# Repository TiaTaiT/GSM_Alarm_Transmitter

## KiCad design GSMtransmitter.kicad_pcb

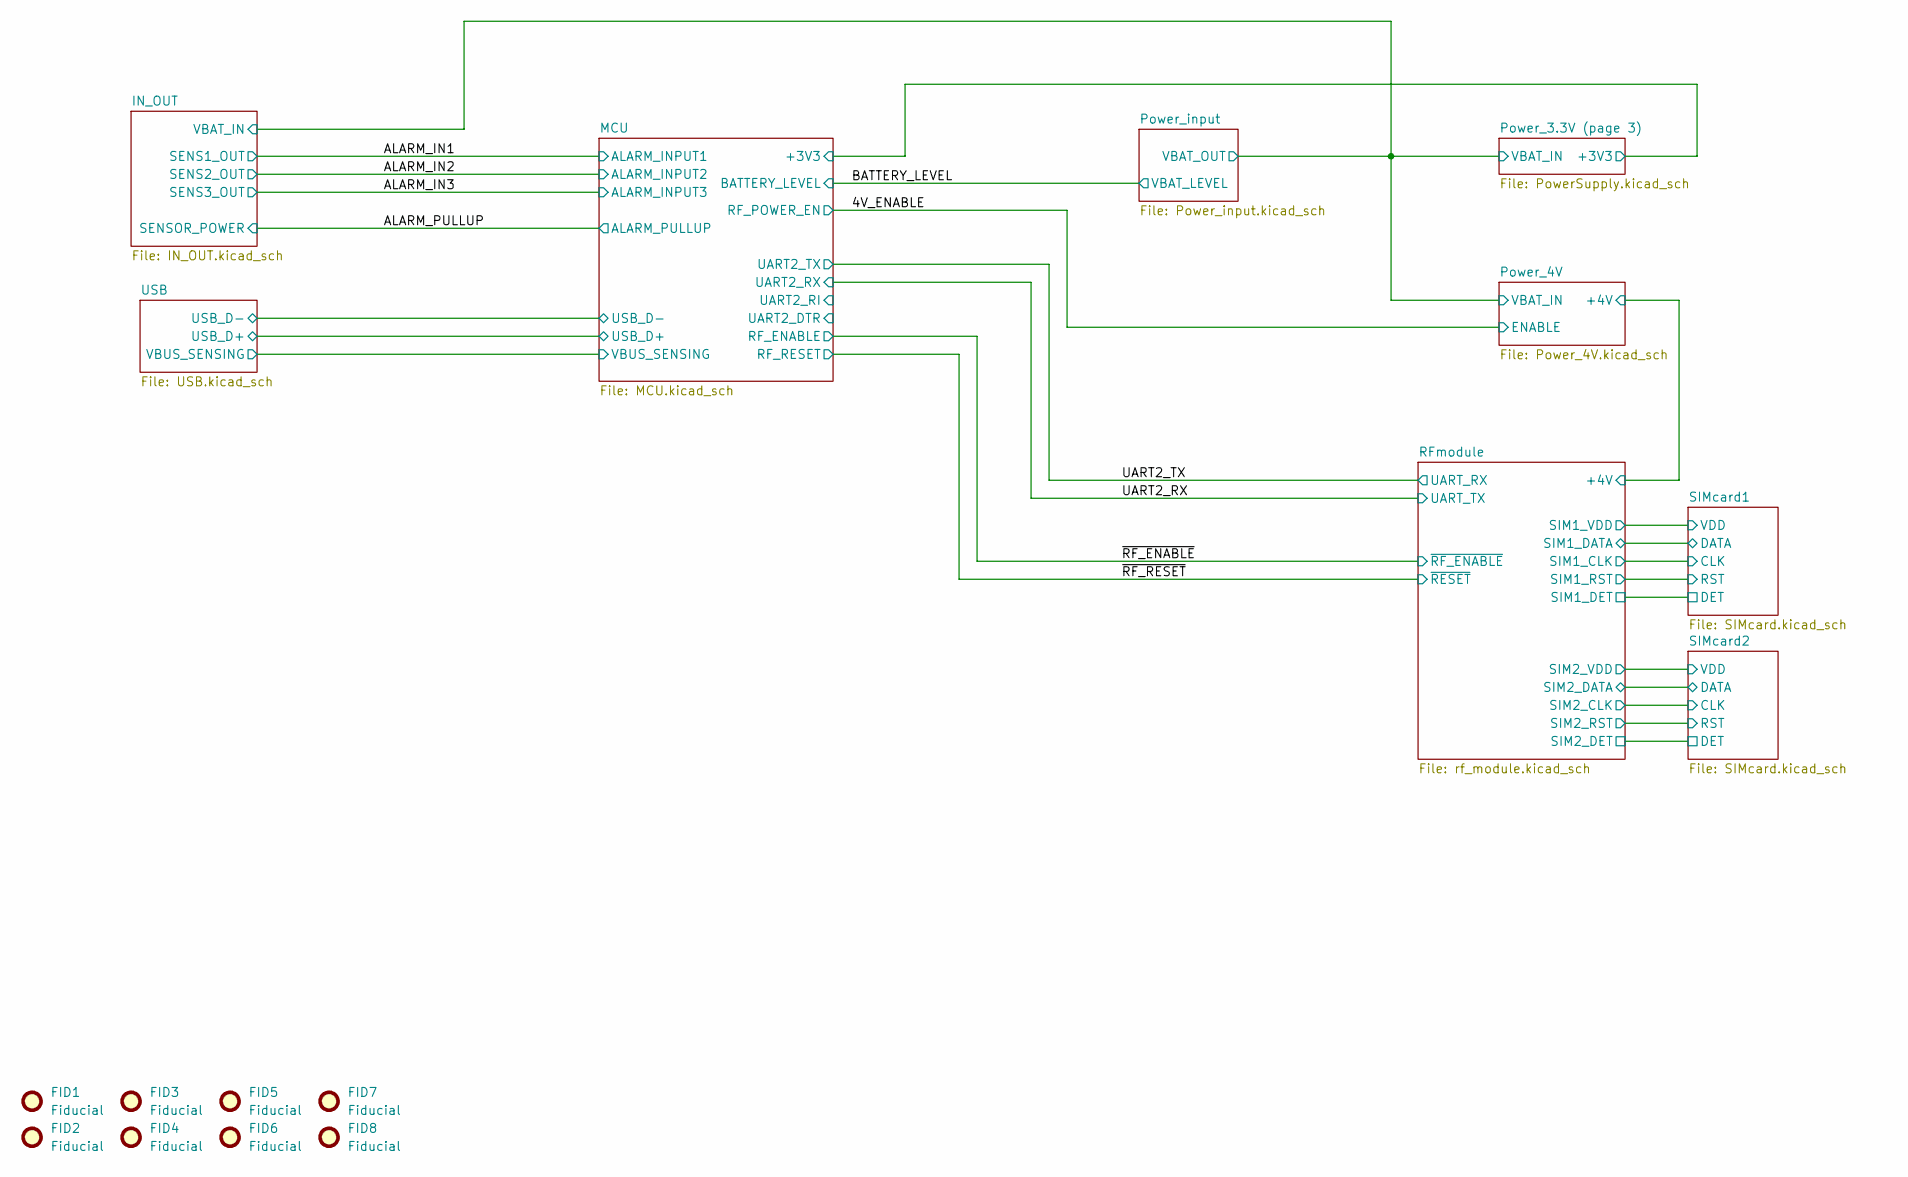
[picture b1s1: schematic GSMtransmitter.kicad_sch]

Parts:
FID1, FID2, FID3, FID4, FID5, FID6, FID7, FID8: Fiducial; Fiducial_1mm_Mask2mm

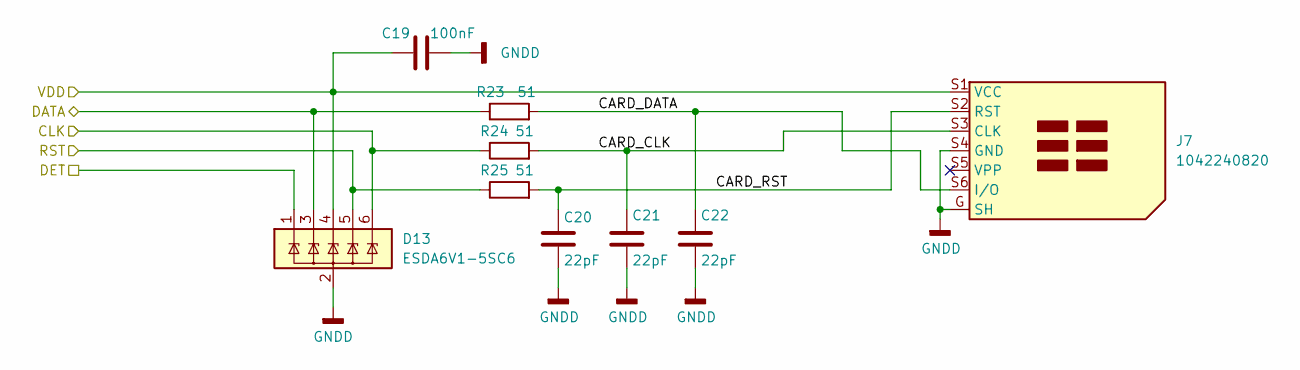
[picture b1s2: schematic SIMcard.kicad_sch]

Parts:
C19: 100nF; C_0805_2012Metric_Pad1.18x1.45mm_HandSolder; MPN CC0805KRX7R8BB104
C20, C21, C22: 22pF; C_0805_2012Metric_Pad1.18x1.45mm_HandSolder; MPN CC0805KRNPO9BN220
D13: ESDA6V1-5SC6; SOT-23-6; MPN ESDA6V1-5SC6
J7: 1042240820; 1042240820_MOLEX; MPN 1042240820
R23, R24, R25: 51; R_0805_2012Metric_Pad1.20x1.40mm_HandSolder; MPN RC0805JR-0751RL

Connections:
/RFmodule/SIM1_CLK: D13.6 (IO5), R24.1; also elsewhere on the board
/RFmodule/SIM1_DATA: D13.3 (IO2), R23.1; also elsewhere on the board
/RFmodule/SIM1_DET: D13.1 (IO1); also elsewhere on the board
/RFmodule/SIM1_RST: D13.5 (IO4), R25.1; also elsewhere on the board
/RFmodule/SIM1_VDD: C19.2, D13.4 (IO3), J7.S1 (VCC); also elsewhere on the board
/SIMcard1/CARD_CLK: C21.2, J7.S3 (CLK), R24.2
/SIMcard1/CARD_DATA: C22.2, J7.S6 (I/O), R23.2
/SIMcard1/CARD_RST: C20.2, J7.S2 (RST), R25.2
GNDD: C19.1, C20.1, C21.1, C22.1, D13.2 (GND), J7.G (SH), J7.S4 (GND); also elsewhere on the board

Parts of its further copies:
C23: 100nF; C_0805_2012Metric_Pad1.18x1.45mm_HandSolder; MPN CC0805KRX7R8BB104
C24, C25, C26: 22pF; C_0805_2012Metric_Pad1.18x1.45mm_HandSolder; MPN CC0805KRNPO9BN220
D14: ESDA6V1-5SC6; SOT-23-6; MPN ESDA6V1-5SC6
J8: 1042240820; 1042240820_MOLEX; MPN 1042240820
R26, R27, R28: 51; R_0805_2012Metric_Pad1.20x1.40mm_HandSolder; MPN RC0805JR-0751RL

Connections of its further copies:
/RFmodule/SIM2_CLK: D14.6 (IO5), R27.1; also elsewhere on the board
/RFmodule/SIM2_DATA: D14.3 (IO2), R26.1; also elsewhere on the board
/RFmodule/SIM2_DET: D14.1 (IO1); also elsewhere on the board
/RFmodule/SIM2_RST: D14.5 (IO4), R28.1; also elsewhere on the board
/RFmodule/SIM2_VDD: C23.2, D14.4 (IO3), J8.S1 (VCC); also elsewhere on the board
/SIMcard2/CARD_CLK: C25.2, J8.S3 (CLK), R27.2
/SIMcard2/CARD_DATA: C26.2, J8.S6 (I/O), R26.2
/SIMcard2/CARD_RST: C24.2, J8.S2 (RST), R28.2
GNDD: C23.1, C24.1, C25.1, C26.1, D14.2 (GND), J8.G (SH), J8.S4 (GND); also elsewhere on the board

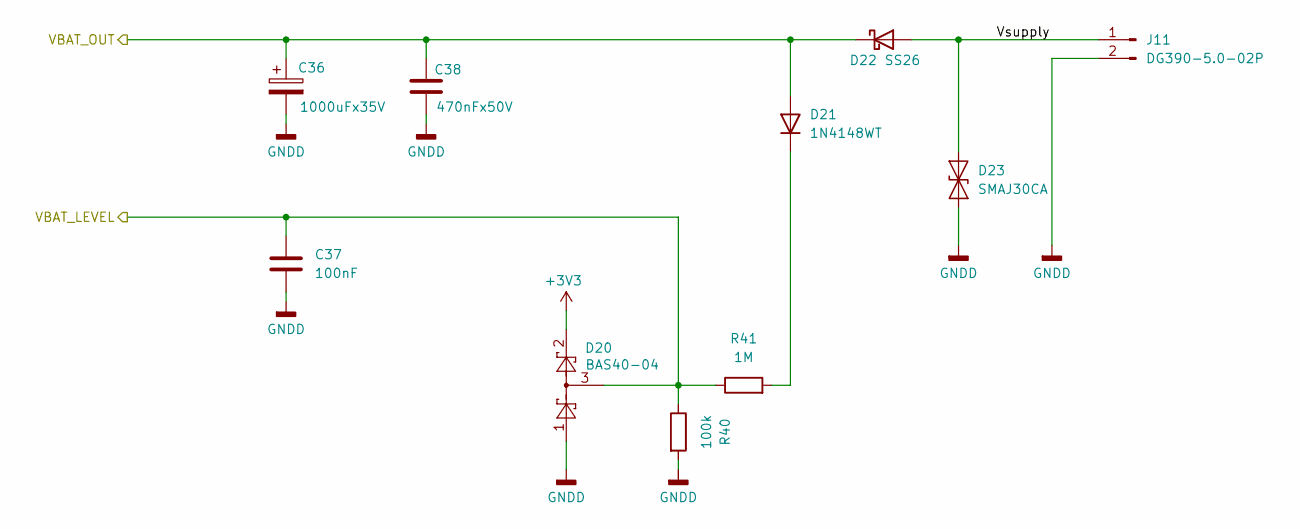
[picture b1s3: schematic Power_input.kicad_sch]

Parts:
C36: 1000uFx35V; CP_Radial_D12.5mm_P5.00mm; MPN B41851F7108M000
C37: 100nF; C_0805_2012Metric_Pad1.18x1.45mm_HandSolder; MPN CC0805KRX7R8BB104
C38: 470nFx50V; C_0805_2012Metric_Pad1.18x1.45mm_HandSolder; MPN CC0805ZRY5V9BB474
D20: BAS40-04; SOT-23; MPN BAS40-04-7-F
D21: 1N4148WT; D_SOD-523; MPN 1N4148WT-7
D22: SS26; D_SMA; MPN SS26
D23: SMAJ30CA; D_SMA; MPN SMAJ30CA
J11: DG390-5.0-02P; DEGSON_DG390-5.0-02P_1x02_P5.0mm_Vertical; MPN DG390-5.0-02P
R40: 100k; R_0805_2012Metric_Pad1.20x1.40mm_HandSolder; MPN RC0805JR-07100KL
R41: 1M; R_0805_2012Metric_Pad1.20x1.40mm_HandSolder; MPN RC0805JR-071ML

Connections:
+3V3: D20.2; also elsewhere on the board
/BATTERY_LEVEL: C37.2, D20.3, R40.1, R41.1; also elsewhere on the board
/IN_OUT/VBAT_IN: C36.1, C38.1, D21.2 (A), D22.1 (K); also elsewhere on the board
/Power_input/Vsupply: D22.2 (A), D23.2 (A2), J11.1
GNDD: C36.2, C37.1, C38.2, D20.1, D23.1 (A1), J11.2, R40.2; also elsewhere on the board
unnamed: D21.1 (K), R41.2

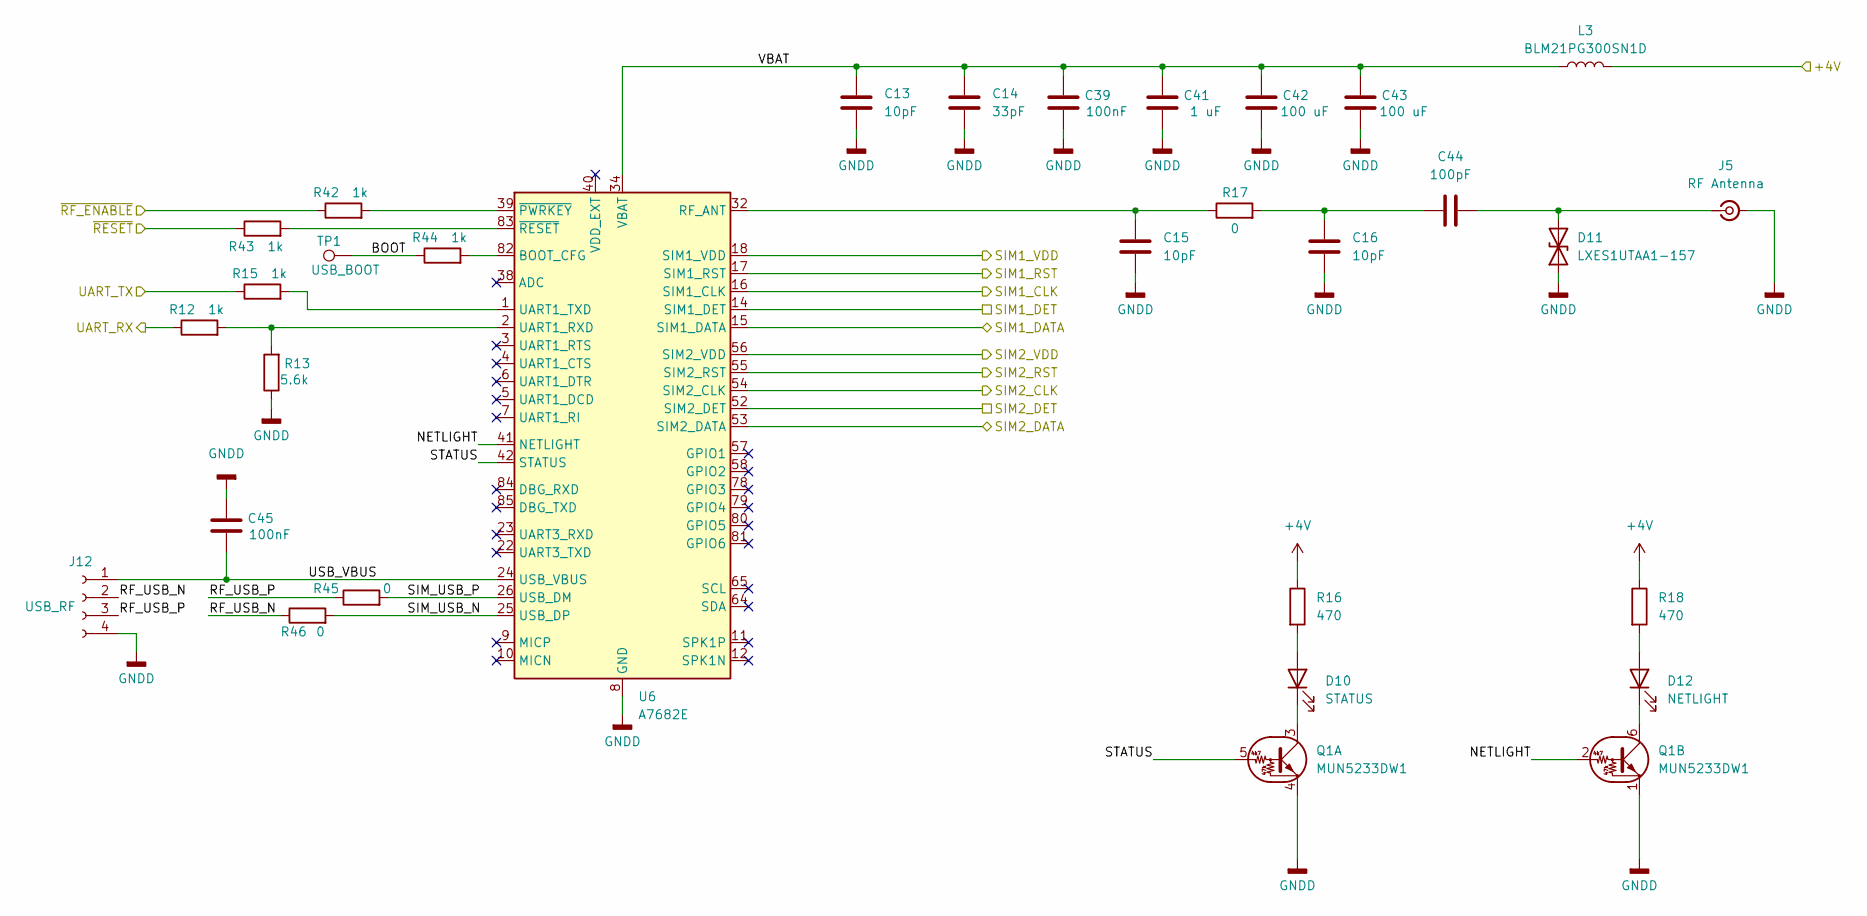
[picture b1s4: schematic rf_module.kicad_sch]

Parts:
C13: 10pF; C_0805_2012Metric_Pad1.18x1.45mm_HandSolder; MPN CC0805JRNPO9BN100
C14: 33pF; C_0805_2012Metric_Pad1.18x1.45mm_HandSolder; MPN CC0805JRNPO9BN330
C15, C16: 10pF; C_0402_1005Metric; MPN CC0402JRNPO9BN100
C39, C45: 100nF; C_0805_2012Metric_Pad1.18x1.45mm_HandSolder; MPN CC0805KRX7R8BB104
C41: 1 uF; C_0805_2012Metric_Pad1.18x1.45mm_HandSolder; MPN CC0805KFX7R9BB105
C42, C43: 100 uF; C_1206_3216Metric_Pad1.33x1.80mm_HandSolder; MPN CC1206MKX5R5BB107
C44: 100pF; C_0402_1005Metric; MPN CC0402JRNPO9BN101
D10: STATUS; LED_0805_2012Metric_Pad1.15x1.40mm_HandSolder; MPN FYLS-0805URC
D11: LXES1UTAA1-157; D_01005_0402Metric; MPN LXES1UTAA1-157
D12: NETLIGHT; LED_0805_2012Metric_Pad1.15x1.40mm_HandSolder; MPN FYLS-0805URC
J5: RF Antenna; SMA_HJ-SMA405; MPN HJ-SMA405
J12: USB_RF; PinHeader_1x04_P1.27mm_Vertical
L3: BLM21PG300SN1D; L_0805_2012Metric; MPN BLM21PG300SN1D
Q1: MUN5233DW1; SOT-363_SC-70-6; MPN MMUN2133LT1G
R12, R15, R42, R43, R44: 1k; R_0805_2012Metric_Pad1.20x1.40mm_HandSolder; MPN RC0805JR-071KL
R13: 5.6k; R_0805_2012Metric_Pad1.20x1.40mm_HandSolder; MPN RC0805JR-075K6L
R16, R18: 470; R_0805_2012Metric_Pad1.20x1.40mm_HandSolder; MPN RC0805JR-07470RL
R17, R45, R46: 0; R_0402_1005Metric; MPN RC0402JR-070RL
TP1: USB_BOOT; TestPoint_Pad_D2.0mm
U6: A7682E; SIMCom_A7682E_LGA-85; MPN A7682E

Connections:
+4V: L3.2, R16.1, R18.1; also elsewhere on the board
/RFmodule/BOOT: R44.1, TP1.1 (1_1)
/RFmodule/NETLIGHT: Q1.2 (B), U6.41 (NETLIGHT)
/RFmodule/RF_USB_N: J12.2, R46.1
/RFmodule/RF_USB_P: J12.3, R45.1
/RFmodule/SIM1_CLK: U6.16 (SIM1_CLK); also elsewhere on the board
/RFmodule/SIM1_DATA: U6.15 (SIM1_DATA); also elsewhere on the board
/RFmodule/SIM1_DET: U6.14 (SIM1_DET); also elsewhere on the board
/RFmodule/SIM1_RST: U6.17 (SIM1_RST); also elsewhere on the board
/RFmodule/SIM1_VDD: U6.18 (SIM1_VDD); also elsewhere on the board
/RFmodule/SIM2_CLK: U6.54 (SIM2_CLK); also elsewhere on the board
/RFmodule/SIM2_DATA: U6.53 (SIM2_DATA); also elsewhere on the board
/RFmodule/SIM2_DET: U6.52 (SIM2_DET); also elsewhere on the board
/RFmodule/SIM2_RST: U6.55 (SIM2_RST); also elsewhere on the board
/RFmodule/SIM2_VDD: U6.56 (SIM2_VDD); also elsewhere on the board
/RFmodule/SIM_USB_N: R46.2, U6.25 (USB_DP)
/RFmodule/SIM_USB_P: R45.2, U6.26 (USB_DM)
/RFmodule/STATUS: Q1.5 (B), U6.42 (STATUS)
/RFmodule/USB_VBUS: C45.1, J12.1, U6.24 (USB_VBUS)
/RFmodule/VBAT: C13.2, C14.2, C39.2, C41.2, C42.2, C43.2, L3.1, U6.34 (VBAT), U6.35 (VBAT)
/UART2_RX: R15.1; also elsewhere on the board
/UART2_TX: R12.1; also elsewhere on the board
/~RF_ENABLE: R42.1; also elsewhere on the board
/~RF_RESET: R43.1; also elsewhere on the board
GNDD: C13.1, C14.1, C15.1, C16.1, C39.1, C41.1, C42.1, C43.1, C45.2, D11.1 (A1), J5.2 (Ext), J12.4, Q1.1 (E), Q1.4 (E), R13.1, U6.8 (GND), U6.13 (GND), U6.19 (GND), U6.21 (GND), U6.27 (GND), U6.30 (GND), U6.31 (GND), U6.33 (GND), U6.36 (GND), U6.37 (GND), U6.45 (GND), U6.63 (GND), U6.66 (GND), U6.67 (GND), U6.69 (GND), U6.70 (GND), U6.71 (GND), U6.72 (GND), U6.73 (GND), U6.74 (GND), U6.75 (GND), U6.76 (GND), U6.77 (GND); also elsewhere on the board
unnamed: C16.2, C44.2, R17.2
unnamed: D10.2 (A), R16.2
unnamed: D10.1 (K), Q1.3 (C)
unnamed: C44.1, D11.2 (A2), J5.1 (In)
unnamed: D12.2 (A), R18.2
unnamed: D12.1 (K), Q1.6 (C)
unnamed: R44.2, U6.82 (BOOT_CFG)
unnamed: C15.2, R17.1, U6.32 (RF_ANT)
unnamed: R12.2, R13.2, U6.2 (UART1_RXD)
unnamed: R15.2, U6.1 (UART1_TXD)
unnamed: R42.2, U6.39 (~PWRKEY)
unnamed: R43.2, U6.83 (~RESET)

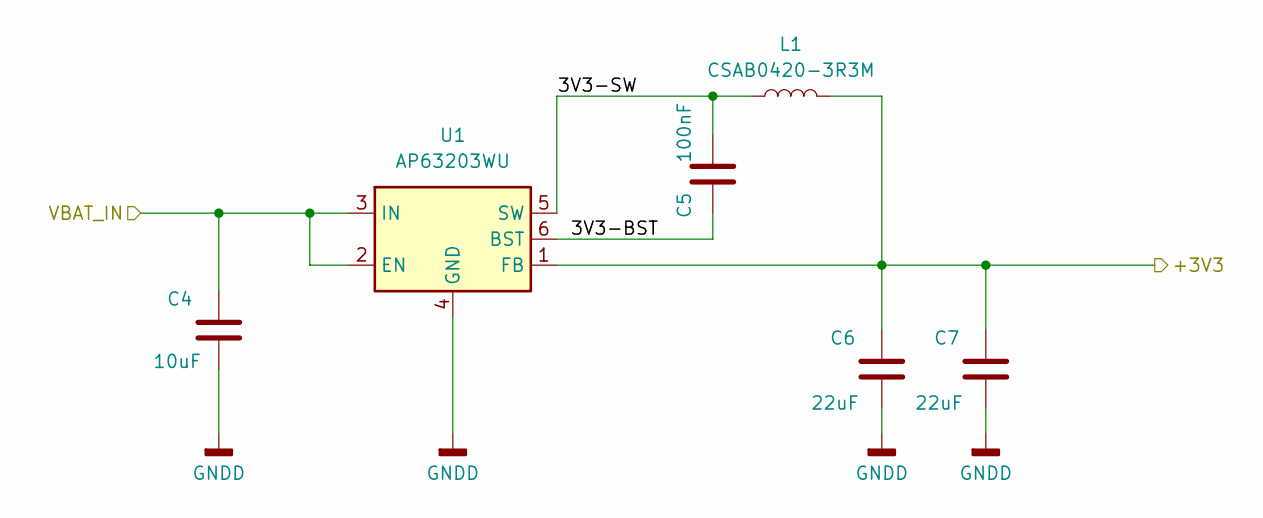
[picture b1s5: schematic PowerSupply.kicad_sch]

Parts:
C4: 10uF; C_0805_2012Metric_Pad1.18x1.45mm_HandSolder; MPN CC0805KKX5R9BB106
C5: 100nF; C_0805_2012Metric_Pad1.18x1.45mm_HandSolder; MPN CC0805KRX7R8BB104
C6, C7: 22uF; C_0805_2012Metric_Pad1.18x1.45mm_HandSolder; MPN CC0805MKX5R8BB226
L1: CSAB0420-3R3M; CSAB0420-4.4x4.4mm; MPN CSAB0420-3R3M
U1: AP63203WU; TSOT-23-6; MPN AP63203WU

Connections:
+3V3: C6.2, C7.2, L1.2, U1.1 (FB); also elsewhere on the board
/IN_OUT/VBAT_IN: C4.2, U1.2 (EN), U1.3 (IN); also elsewhere on the board
/Power_3.3V (page 3)/3V3-BST: C5.1, U1.6 (BST)
/Power_3.3V (page 3)/3V3-SW: C5.2, L1.1, U1.5 (SW)
GNDD: C4.1, C6.1, C7.1, U1.4 (GND); also elsewhere on the board

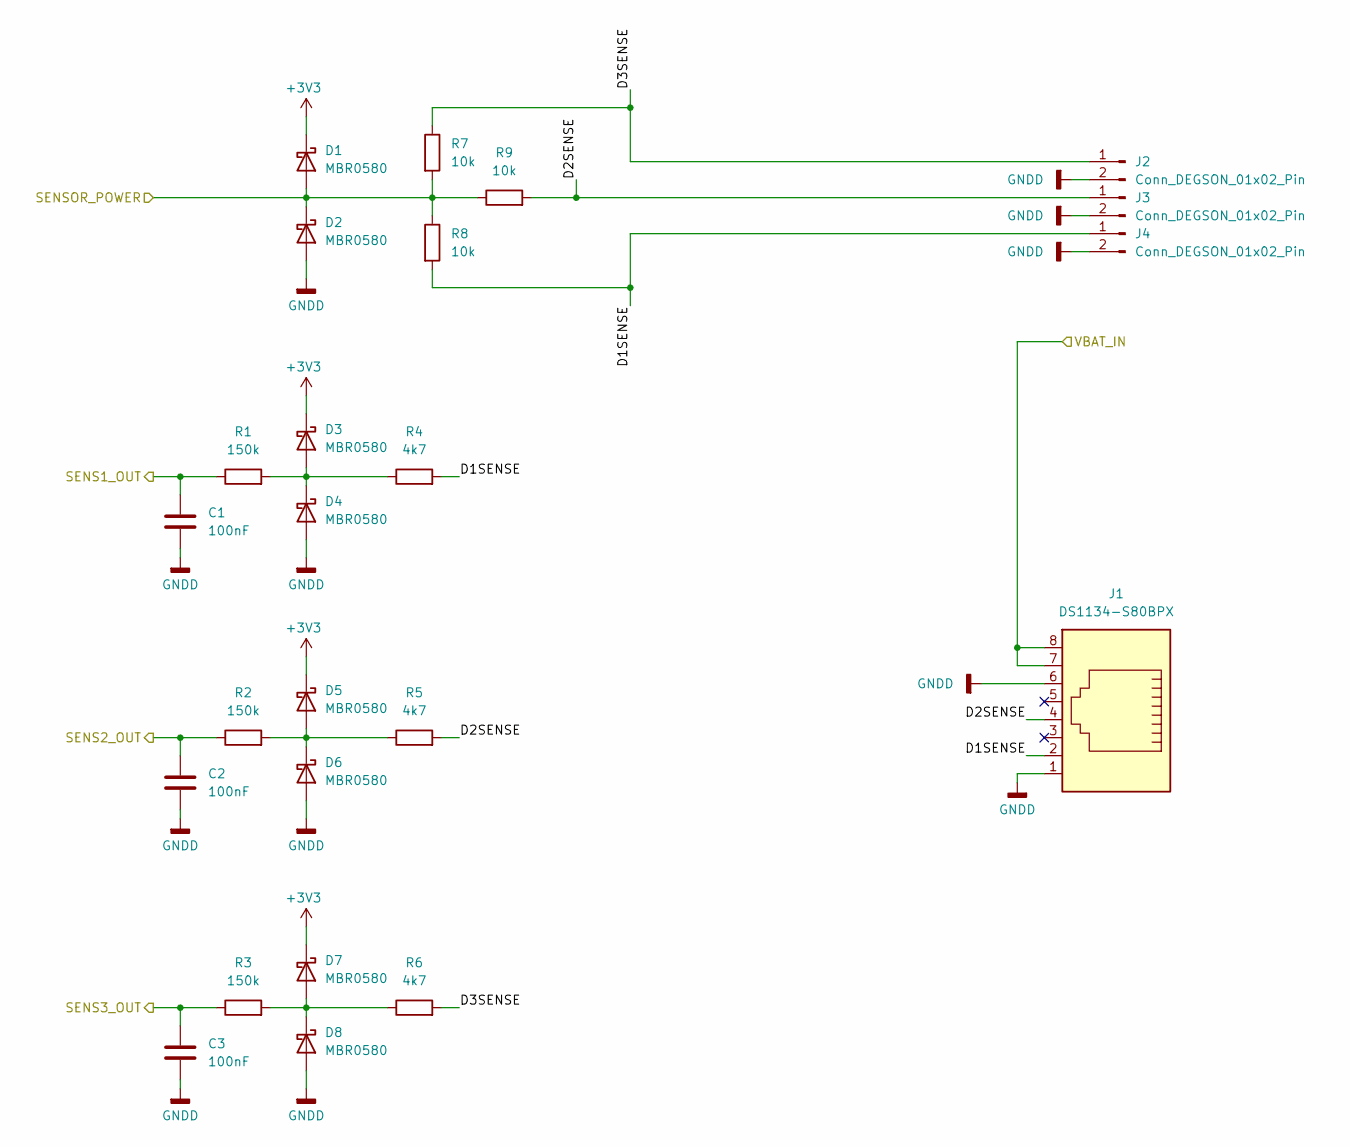
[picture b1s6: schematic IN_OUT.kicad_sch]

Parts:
C1, C2, C3: 100nF; C_0805_2012Metric_Pad1.18x1.45mm_HandSolder; MPN CC0805KRX7R8BB104
D1, D2, D3, D4, D5, D6, D7, D8: MBR0580; D_SOD-123; MPN MBR0580
J1: DS1134-S80BPX; RJ45_DS1134-8P8CX_Horizontal; MPN DS1134-S80BPX
J2, J3, J4: Conn_DEGSON_01x02_Pin; DEGSON_DG390-5.0-02P_1x02_P5.0mm_Vertical; MPN DG390-5.0-02P
R1, R2, R3: 150k; R_0805_2012Metric_Pad1.20x1.40mm_HandSolder; MPN RC0805JR-07150KL
R4, R5, R6: 4k7; R_0805_2012Metric_Pad1.20x1.40mm_HandSolder; MPN RC0805JR-074K7L
R7, R8, R9: 10k; R_0805_2012Metric_Pad1.20x1.40mm_HandSolder; MPN RC0805FR-0710KL

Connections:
+3V3: D1.1 (K), D3.1 (K), D5.1 (K), D7.1 (K); also elsewhere on the board
/ALARM_IN1: C1.2, R1.1; also elsewhere on the board
/ALARM_IN2: C2.2, R2.1; also elsewhere on the board
/ALARM_IN3: C3.2, R3.1; also elsewhere on the board
/ALARM_PULLUP: D1.2 (A), D2.1 (K), R7.2, R8.1, R9.1; also elsewhere on the board
/IN_OUT/D1SENSE: J1.2, J4.1, R4.2, R8.2
/IN_OUT/D2SENSE: J1.4, J3.1, R5.2, R9.2
/IN_OUT/D3SENSE: J2.1, R6.2, R7.1
/IN_OUT/VBAT_IN: J1.7, J1.8; also elsewhere on the board
GNDD: C1.1, C2.1, C3.1, D2.2 (A), D4.2 (A), D6.2 (A), D8.2 (A), J1.1, J1.6, J2.2, J3.2, J4.2; also elsewhere on the board
unnamed: D3.2 (A), D4.1 (K), R1.2, R4.1
unnamed: D5.2 (A), D6.1 (K), R2.2, R5.1
unnamed: D7.2 (A), D8.1 (K), R3.2, R6.1

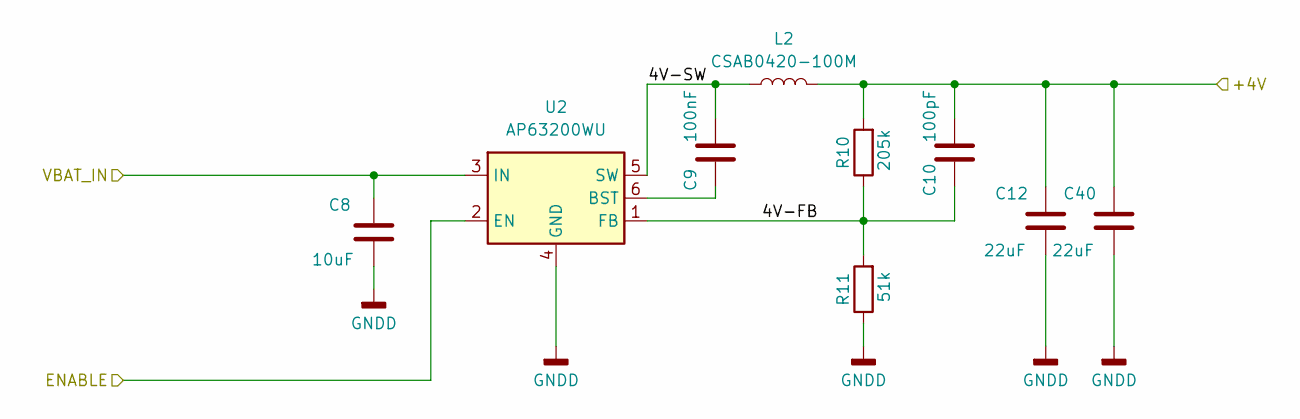
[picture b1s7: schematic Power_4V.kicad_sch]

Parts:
C8: 10uF; C_0805_2012Metric_Pad1.18x1.45mm_HandSolder; MPN CC0805KKX5R9BB106
C9: 100nF; C_0805_2012Metric_Pad1.18x1.45mm_HandSolder; MPN CC0805KRX7R8BB104
C10: 100pF; C_0805_2012Metric_Pad1.18x1.45mm_HandSolder; MPN CC0805JRNPO9BN101
C12, C40: 22uF; C_0805_2012Metric_Pad1.18x1.45mm_HandSolder; MPN CC0805MKX5R8BB226
L2: CSAB0420-100M; CSAB0420-4.4x4.4mm; MPN CSAB0420-100M
R10: 205k; R_0805_2012Metric_Pad1.20x1.40mm_HandSolder; MPN RC0805FR-07205KL
R11: 51k; R_0805_2012Metric_Pad1.20x1.40mm_HandSolder; MPN RC0805FR-0751KL
U2: AP63200WU; TSOT-23-6; MPN AP63200WU

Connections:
+4V: C10.2, C12.2, C40.2, L2.2, R10.2; also elsewhere on the board
/4V_ENABLE: U2.2 (EN); also elsewhere on the board
/IN_OUT/VBAT_IN: C8.2, U2.3 (IN); also elsewhere on the board
/Power_4V/4V-FB: C10.1, R10.1, R11.2, U2.1 (FB)
/Power_4V/4V-SW: C9.2, L2.1, U2.5 (SW)
GNDD: C8.1, C12.1, C40.1, R11.1, U2.4 (GND); also elsewhere on the board
unnamed: C9.1, U2.6 (BST)

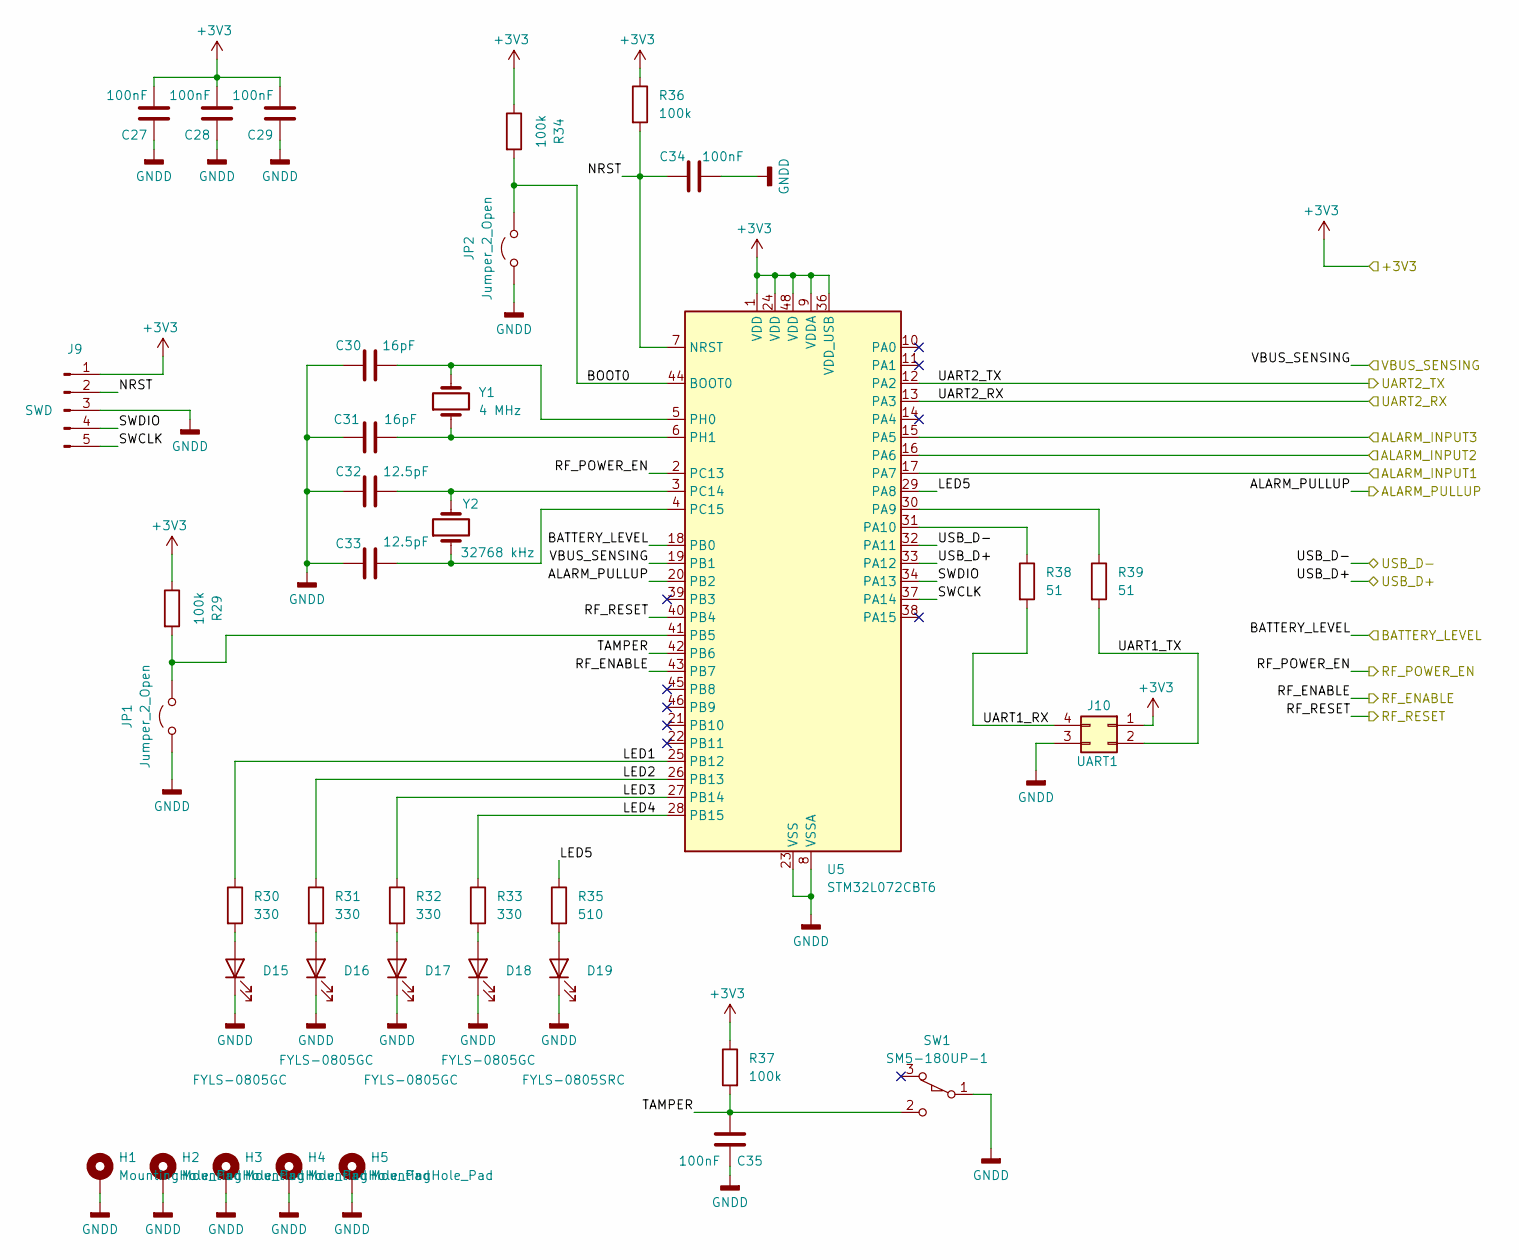
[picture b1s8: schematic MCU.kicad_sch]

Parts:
C27, C28, C29, C34, C35: 100nF; C_0805_2012Metric_Pad1.18x1.45mm_HandSolder; MPN CC0805KRX7R8BB104
C30, C31: 16pF; C_0805_2012Metric_Pad1.18x1.45mm_HandSolder; MPN CC0805JRNPO0BN160
C32, C33: 12.5pF; C_0805_2012Metric_Pad1.18x1.45mm_HandSolder; MPN CC0805JRNPO9BN120
D15, D16, D17, D18: FYLS-0805GC; LED_0805_2012Metric_Pad1.15x1.40mm_HandSolder; MPN FYLS-0805GC
D19: FYLS-0805SRC; LED_0805_2012Metric_Pad1.15x1.40mm_HandSolder; MPN FYLS-0805SRC
H1, H2, H3, H4, H5: MountingHole_Pad; MountingHole_3.2mm_M3_Pad_Via
J9: SWD; PinHeader_1x05_P2.54mm_Vertical; MPN DS1021-1x5SF11-B
J10: UART1; PinSocket_2x02_P2.54mm_Vertical; MPN DS1023-2*2SF11
JP1, JP2: Jumper_2_Open; PinHeader_1x02_P2.54mm_Vertical; MPN DS1021-1x2SF11-B
R29, R34, R36, R37: 100k; R_0805_2012Metric_Pad1.20x1.40mm_HandSolder; MPN RC0805JR-07100KL
R30, R31, R32, R33: 330; R_0805_2012Metric_Pad1.20x1.40mm_HandSolder; MPN RC0805JR-07330RL
R35: 510; R_0805_2012Metric_Pad1.20x1.40mm_HandSolder; MPN RC0805JR-07510RL
R38, R39: 51; R_0805_2012Metric_Pad1.20x1.40mm_HandSolder; MPN RC0805JR-0751RL
SW1: SM5-180UP-1; SW_XKB_SM5-180UP-1; MPN SM5-470UP-1
U5: STM32L072CBT6; LQFP-48_7x7mm_P0.5mm; MPN STM32L072CBT6
Y1: 4 MHz; Crystal_SMD_HC49-SD; MPN SJK-6C-4.000-16-30-100-C-50-H
Y2: 32768 kHz; Crystal_SMD_EuroQuartz_EQ161-2Pin_3.2x1.5mm_HandSoldering; MPN ABS07-32.768KHZ-T

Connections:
+3V3: C27.2, C28.2, C29.2, J9.1, J10.1, R29.1, R34.1, R36.1, R37.1, U5.1 (VDD), U5.9 (VDDA), U5.24 (VDD), U5.36 (VDD_USB), U5.48 (VDD); also elsewhere on the board
/4V_ENABLE: U5.2 (PC13); also elsewhere on the board
/ALARM_IN1: U5.17 (PA7); also elsewhere on the board
/ALARM_IN2: U5.16 (PA6); also elsewhere on the board
/ALARM_IN3: U5.15 (PA5); also elsewhere on the board
/ALARM_PULLUP: U5.20 (PB2); also elsewhere on the board
/BATTERY_LEVEL: U5.18 (PB0); also elsewhere on the board
/MCU/BOOT0: JP2.2 (B), R34.2, U5.44 (BOOT0)
/MCU/LED1: R30.1, U5.25 (PB12)
/MCU/LED2: R31.1, U5.26 (PB13)
/MCU/LED3: R32.1, U5.27 (PB14)
/MCU/LED4: R33.1, U5.28 (PB15)
/MCU/LED5: R35.1, U5.29 (PA8)
/MCU/NRST: C34.1, J9.2, R36.2, U5.7 (NRST)
/MCU/SWCLK: J9.5, U5.37 (PA14)
/MCU/SWDIO: J9.4, U5.34 (PA13)
/MCU/TAMPER: C35.2, R37.2, SW1.2 (B), U5.42 (PB6)
/MCU/UART1_RX: J10.4, R38.2
/MCU/UART1_TX: J10.2, R39.2
/MCU/USB_D+: U5.33 (PA12); also elsewhere on the board
/MCU/USB_D-: U5.32 (PA11); also elsewhere on the board
/MCU/VBUS_SENSING: U5.19 (PB1); also elsewhere on the board
/UART2_RX: U5.13 (PA3); also elsewhere on the board
/UART2_TX: U5.12 (PA2); also elsewhere on the board
/~RF_ENABLE: U5.43 (PB7); also elsewhere on the board
/~RF_RESET: U5.40 (PB4); also elsewhere on the board
GNDD: C27.1, C28.1, C29.1, C30.1, C31.1, C32.1, C33.1, C34.2, C35.1, D15.1 (K), D16.1 (K), D17.1 (K), D18.1 (K), D19.1 (K), H1.1 (1_1), H2.1 (1_1), H3.1 (1_1), H4.1 (1_1), H5.1 (1_1), J9.3, J10.3, JP1.1 (A), JP2.1 (A), SW1.1 (A), U5.8 (VSSA), U5.23 (VSS), U5.35 (VSS), U5.47 (VSS); also elsewhere on the board
unnamed: D15.2 (A), R30.2
unnamed: D16.2 (A), R31.2
unnamed: D17.2 (A), R32.2
unnamed: D18.2 (A), R33.2
unnamed: D19.2 (A), R35.2
unnamed: JP1.2 (B), R29.2, U5.41 (PB5)
unnamed: R39.1, U5.30 (PA9)
unnamed: R38.1, U5.31 (PA10)
unnamed: C32.2, U5.3 (PC14), Y2.2
unnamed: C33.2, U5.4 (PC15), Y2.1
unnamed: C30.2, U5.5 (PH0), Y1.2
unnamed: C31.2, U5.6 (PH1), Y1.1

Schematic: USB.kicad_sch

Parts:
C17, C18: 100nF; C_0805_2012Metric_Pad1.18x1.45mm_HandSolder; MPN CC0805KRX7R8BB104
J6: USB-C; JST_PH_B6B-PH-K_1x06_P2.00mm_Vertical; MPN B6B-PH-K
R19: 47k; R_0805_2012Metric_Pad1.20x1.40mm_HandSolder; MPN RC0805JR-0747KL
R20: 100k; R_0805_2012Metric_Pad1.20x1.40mm_HandSolder; MPN RC0805JR-07100KL
R21, R22: 5.1k; R_0805_2012Metric_Pad1.20x1.40mm_HandSolder; MPN RC0805JR-075K1L
U4: USBLC6-2SC6; SOT-23-6; MPN USBLC6-2SC6

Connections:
/MCU/USB_D+: U4.4 (I/O2); also elsewhere on the board
/MCU/USB_D-: U4.6 (I/O1); also elsewhere on the board
/MCU/VBUS_SENSING: C17.2, R19.1, R20.1; also elsewhere on the board
/USB/USB_CC1: J6.5, R21.1
/USB/USB_CC2: J6.4, R22.1
/USB/USB_N: J6.3, U4.1 (I/O1)
/USB/USB_P: J6.2, U4.3 (I/O2)
/USB/USB_VBUS: C18.2, J6.6, R20.2, U4.5 (VBUS)
GNDD: C17.1, C18.1, J6.1, R19.2, R21.2, R22.2, U4.2 (GND); also elsewhere on the board

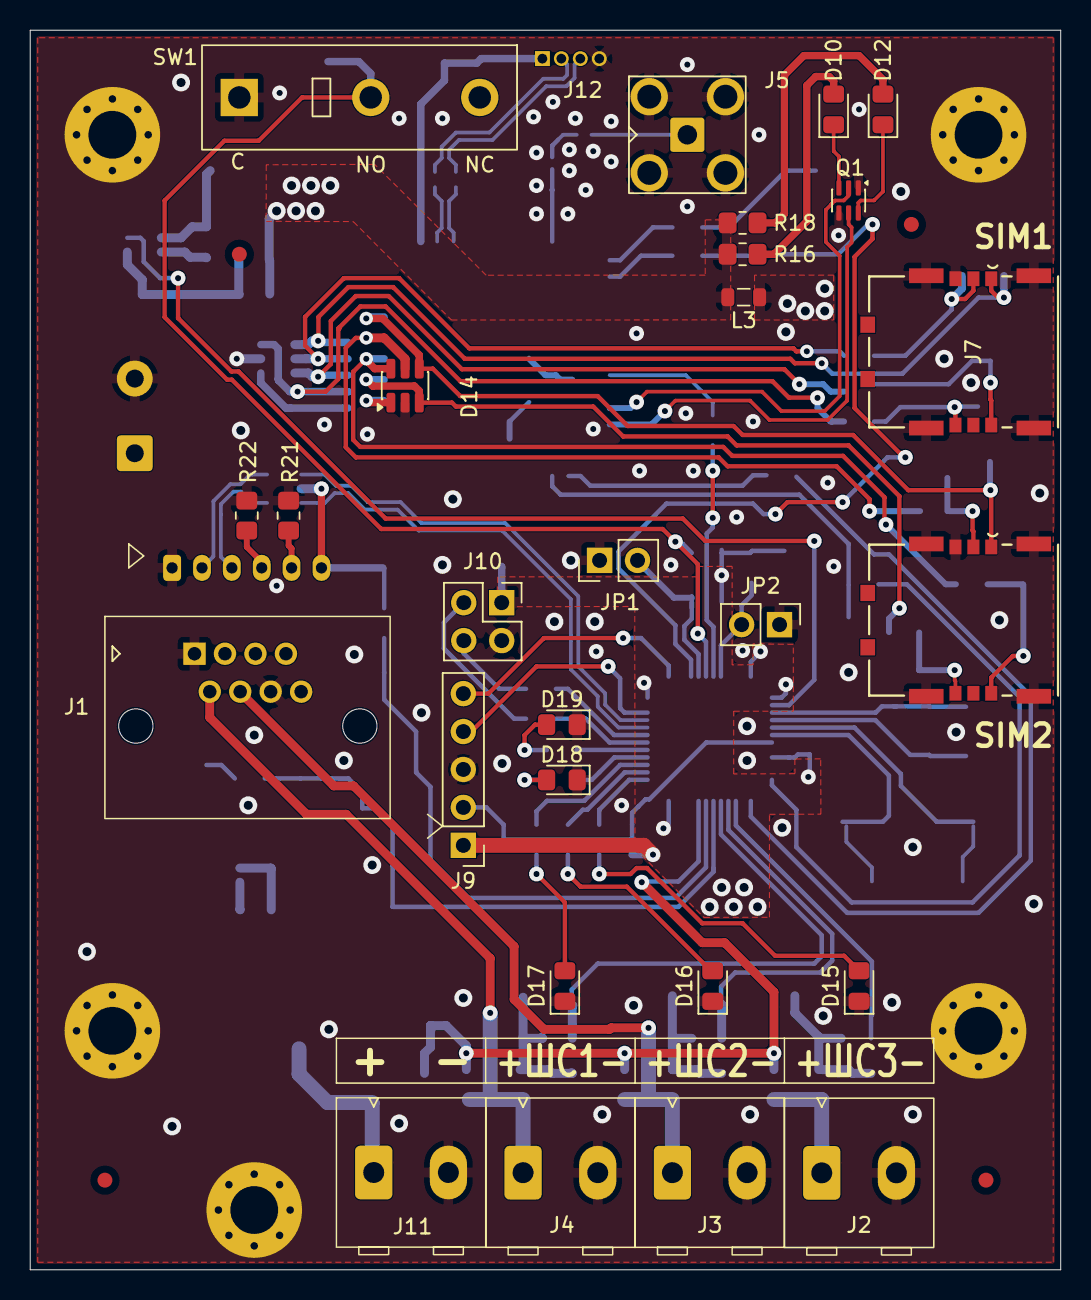
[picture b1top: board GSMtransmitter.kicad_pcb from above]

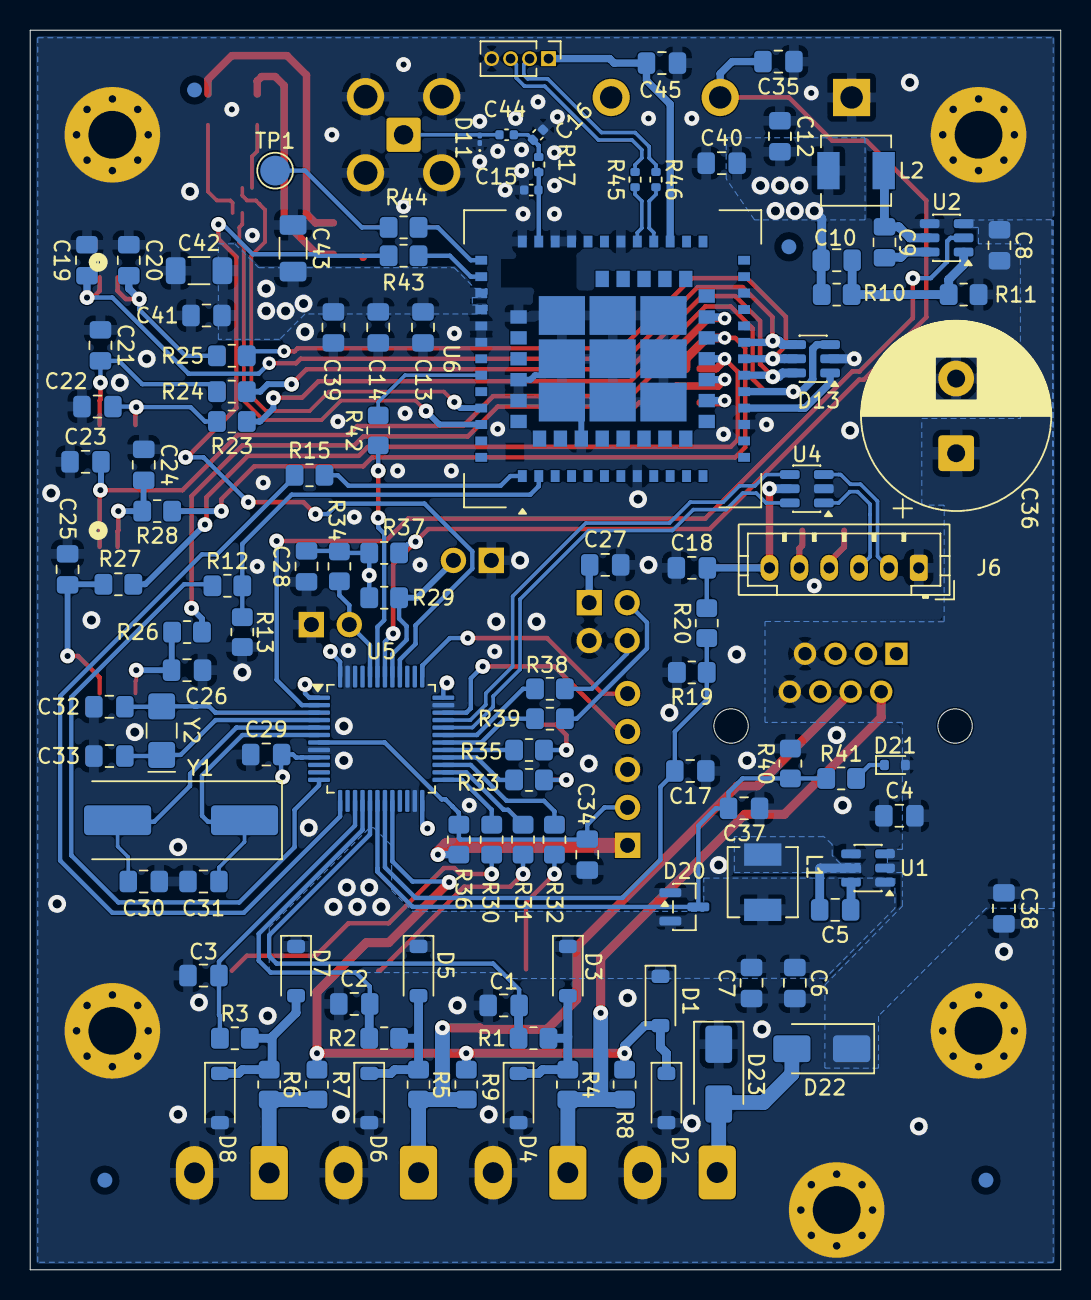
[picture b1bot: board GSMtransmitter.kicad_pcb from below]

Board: 2 copper layers, 69.0 x 83.0 mm, 151 parts (115 on the bottom side), 96 nets.

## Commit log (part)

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2025-03-21 STM32L052 instead STM32L051
2025-03-21 Wrong 32kHz clock pins fixed
2025-03-24 32kHz replaced
2025-03-28 Inductance was replaced
2025-04-16 USB pinout fixed
2025-07-29 Minor changes in PCB for manufacturing
2025-11-07 DEGSON f.mask pad fixed
